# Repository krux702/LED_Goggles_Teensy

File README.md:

# LED_Goggles_Teensy

LED Driver board and support code for Mk3 LED Goggles

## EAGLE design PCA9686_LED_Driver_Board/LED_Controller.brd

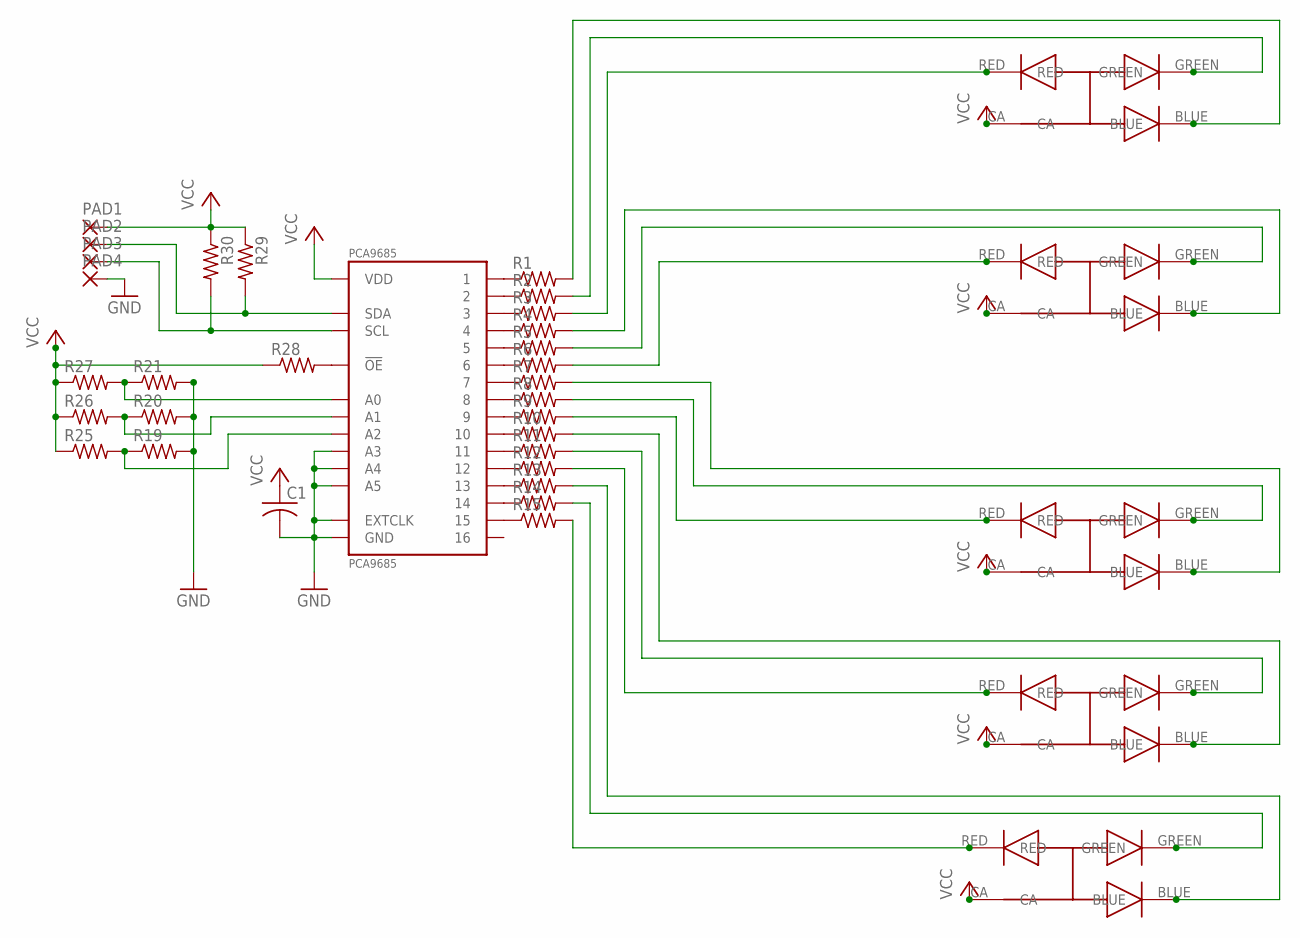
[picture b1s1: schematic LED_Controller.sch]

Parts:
C1: C-USC0402; C0402
PAD1, PAD2, PAD3, PAD4: SMD2; SMD1,27-2,54
PCA9685: PCA9685; HVQFN28
R1, R2, R3, R4, R5, R6, R7, R8, R9, R10, R11, R12, R13, R14, R15, R19, R20, R21, R25, R26, R27, R28, R29, R30: R-US_R0402; R0402
U$2, U$3, U$4, U$5, U$6: CLV1A-FKB

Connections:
GND: C1.2, PAD4.1, PCA9685.4 (A3), PCA9685.5 (A4), PCA9685.14 (GND), PCA9685.24 (A5), PCA9685.25 (EXTCLK), PCA9685.PAD (GND), R19.2, R20.2, R21.2
unnamed: R7.2, U$4.BLUE
unnamed: R2.2, U$6.GREEN
unnamed: PCA9685.2 (A1), R20.1, R26.2
unnamed: R15.2, U$2.RED
unnamed: R14.2, U$2.GREEN
unnamed: R13.2, U$2.BLUE
unnamed: PCA9685.6 (1), R1.1
unnamed: PCA9685.7 (2), R2.1
unnamed: PCA9685.8 (3), R3.1
unnamed: R12.2, U$3.RED
unnamed: R11.2, U$3.GREEN
unnamed: R10.2, U$3.BLUE
unnamed: PCA9685.9 (4), R4.1
unnamed: PCA9685.10 (5), R5.1
unnamed: PCA9685.11 (6), R6.1
unnamed: R9.2, U$4.RED
unnamed: R8.2, U$4.GREEN
unnamed: PCA9685.12 (7), R7.1
unnamed: PCA9685.13 (8), R8.1
unnamed: PCA9685.15 (9), R9.1
unnamed: PCA9685.16 (10), R10.1
unnamed: R6.2, U$5.RED
unnamed: R5.2, U$5.GREEN
unnamed: R4.2, U$5.BLUE
unnamed: PCA9685.17 (11), R11.1
unnamed: PCA9685.18 (12), R12.1
unnamed: PCA9685.19 (13), R13.1
unnamed: R3.2, U$6.RED
unnamed: PCA9685.20 (14), R14.1
unnamed: PCA9685.21 (15), R15.1
unnamed: R1.2, U$6.BLUE
unnamed: PCA9685.23 (!OE), R28.2
unnamed: PCA9685.3 (A2), R19.1, R25.2
unnamed: PAD2.1, PCA9685.27 (SDA), R29.2
unnamed: PAD3.1, PCA9685.26 (SCL), R30.2
unnamed: PCA9685.1 (A0), R21.1, R27.2
VCC: C1.1, PAD1.1, PCA9685.28 (VDD), R25.1, R26.1, R27.1, R28.1, R29.1, R30.1, U$2.CA, U$3.CA, U$4.CA, U$5.CA, U$6.CA

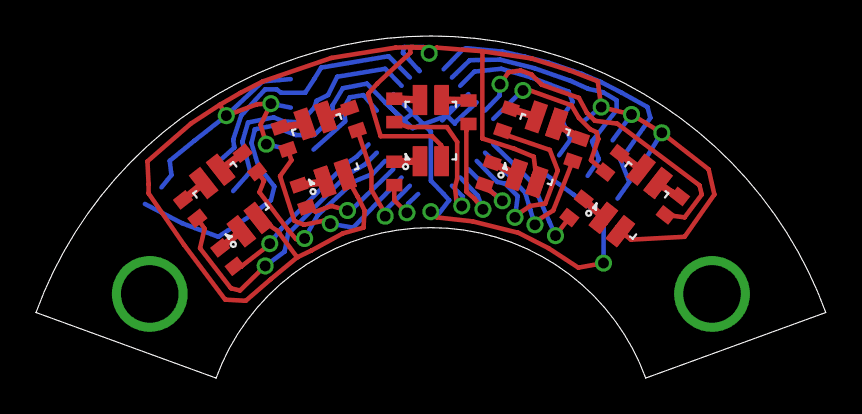
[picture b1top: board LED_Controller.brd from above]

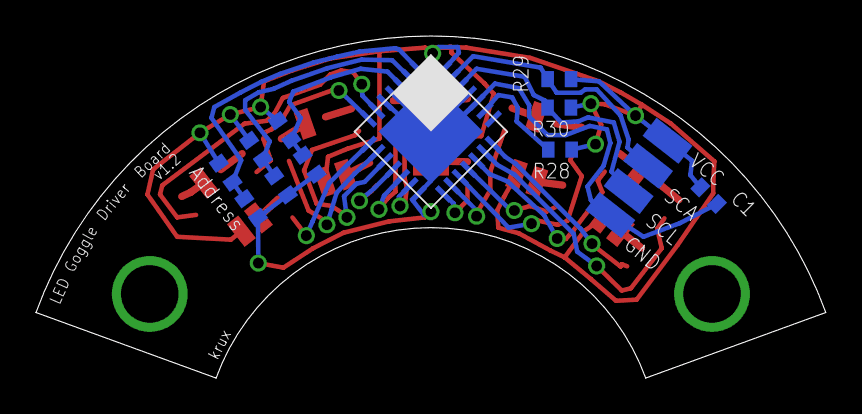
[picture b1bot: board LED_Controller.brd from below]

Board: 2 copper layers, 43.9 x 19.0 mm, 35 parts (15 on the bottom side), 38 nets.

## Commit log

2018-03-08 Imported circa 2013 project into GitHub
